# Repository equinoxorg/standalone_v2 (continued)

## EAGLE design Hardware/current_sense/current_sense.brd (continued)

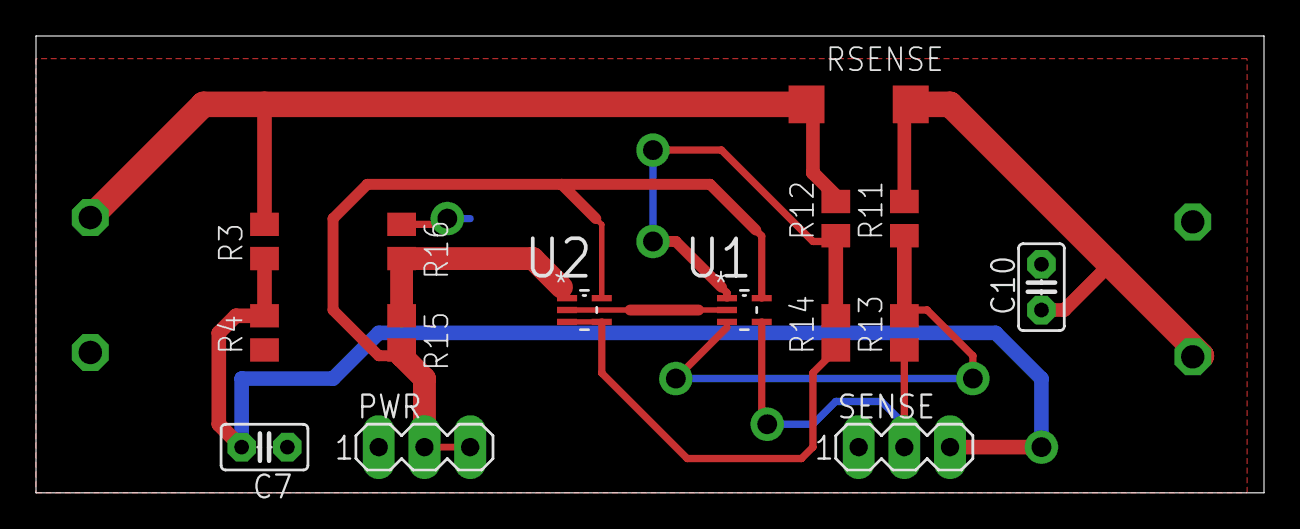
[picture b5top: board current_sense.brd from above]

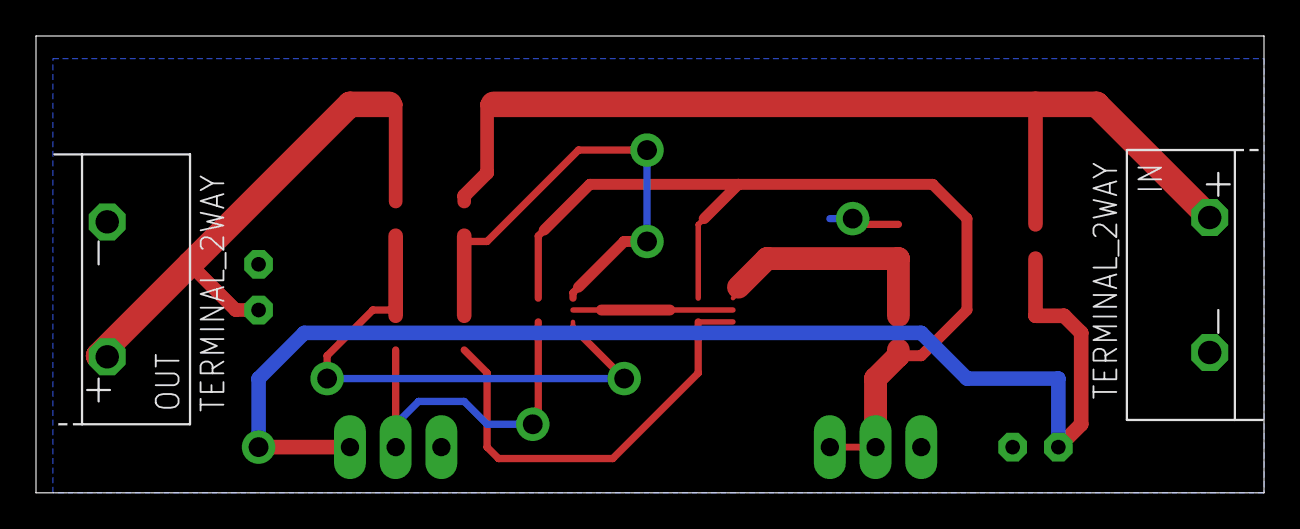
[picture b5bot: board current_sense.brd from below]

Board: 2 copper layers, 68.2 x 25.4 mm, 17 parts (2 on the bottom side), 11 nets.

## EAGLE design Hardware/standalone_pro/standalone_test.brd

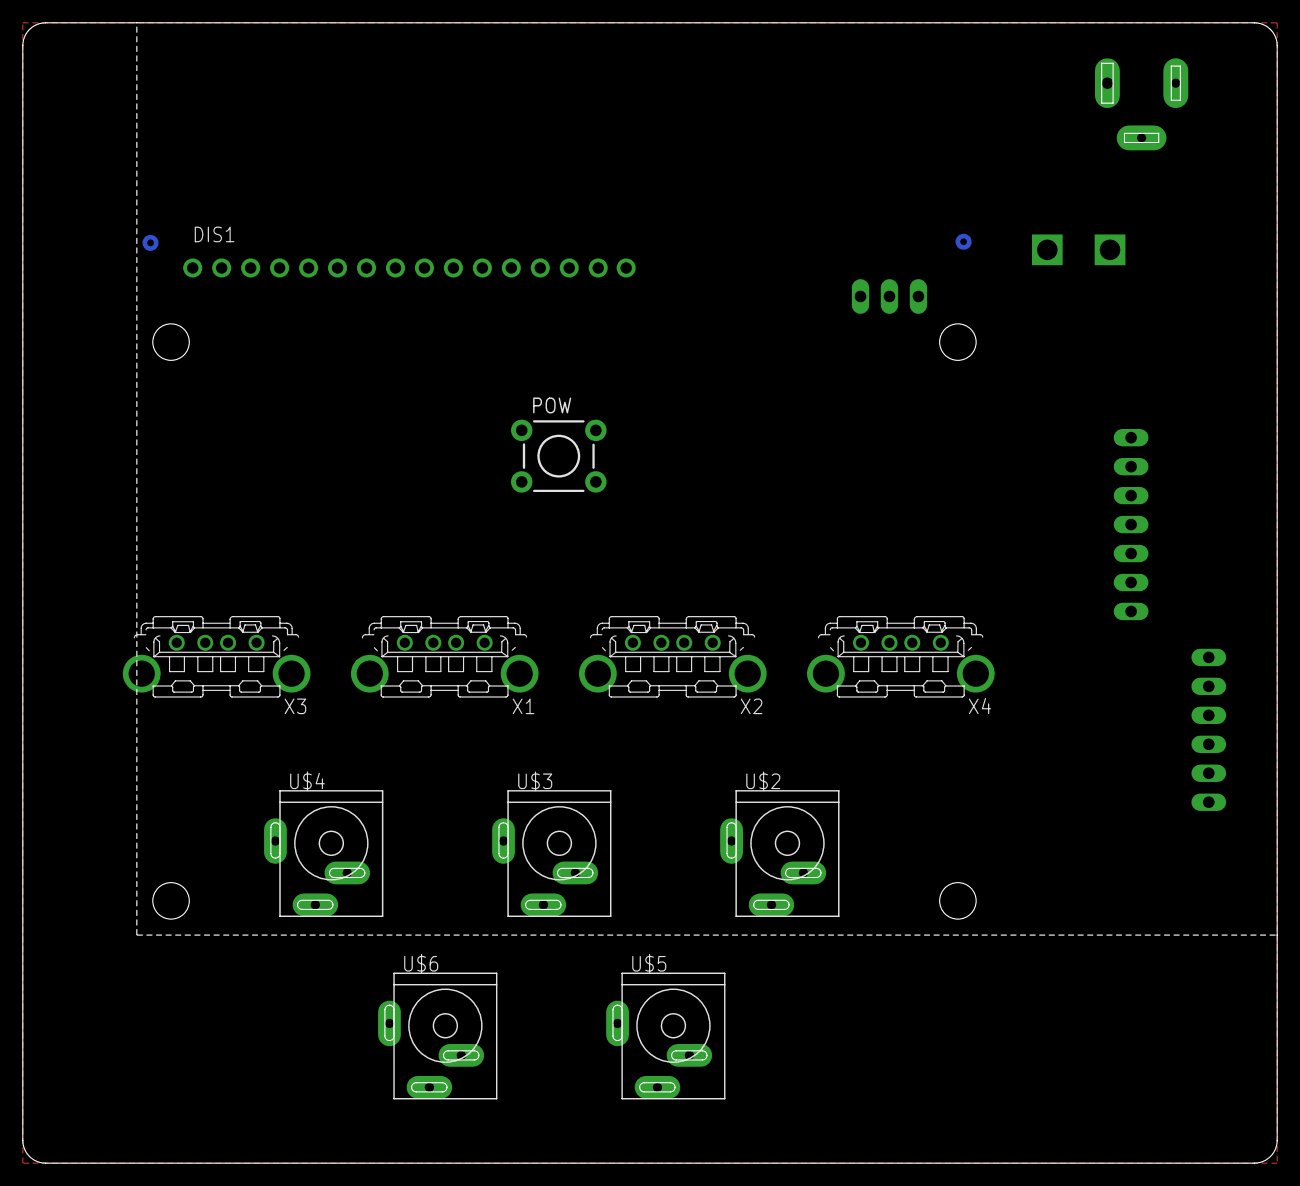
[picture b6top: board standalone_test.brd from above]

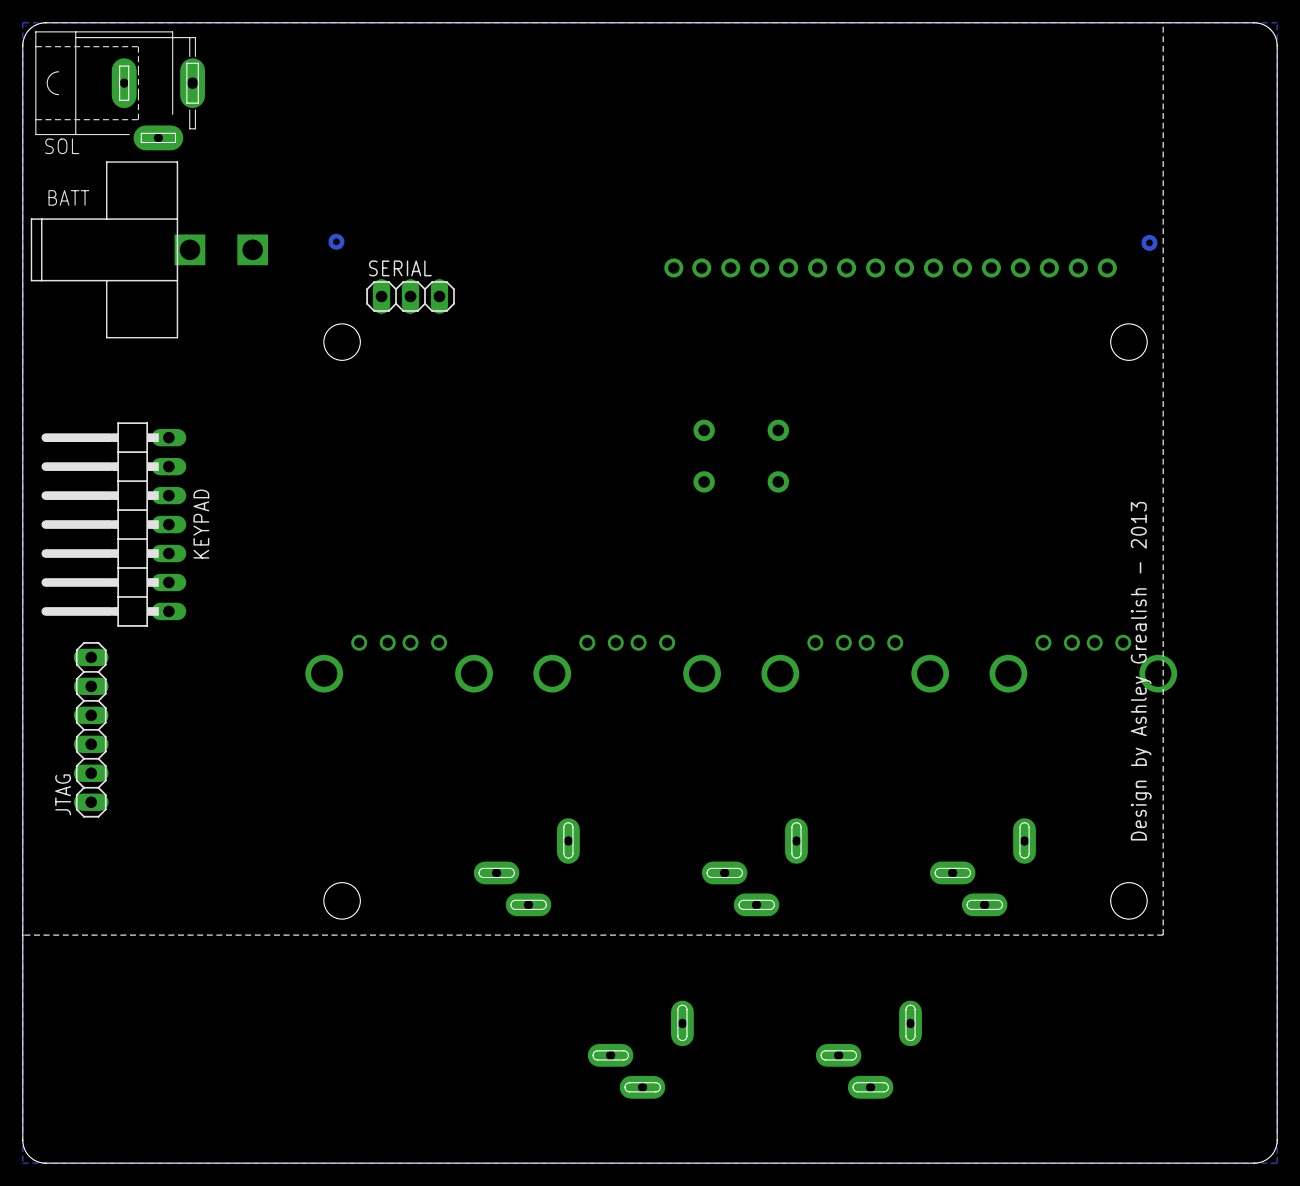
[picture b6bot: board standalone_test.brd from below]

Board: 2 copper layers, 110.0 x 100.0 mm, 17 parts (5 on the bottom side), 5 nets, no tracks yet.

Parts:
BATT: CON_MOLEX_39_29_1028; MOLEX_39_29_1028
DIS1: LCD_16X2_R2
JTAG: 1X06
KEYPAD: 1X07/90
POW: TACTILE-PTH
SERIAL: 1X03
SOL: SPC4077
U$1: EQUINOX_LOGO_LARGE
U$2, U$3, U$4, U$5, U$6: KYCON_KLDVX-0202; KYCON_KLVDX_2020_B
X1, X2, X3, X4: KUSBVX

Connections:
GND: BATT.P$2, SERIAL.3, SOL.1, SOL.2, U$4.2, U$5.2, U$5.3, U$6.2, U$6.3, X1.4, X1.M1, X1.M2, X2.4, X2.M1, X2.M2, X3.4, X3.M1, X3.M2, X4.4, X4.M1, X4.M2
unnamed: DIS1.7, DIS1.8, DIS1.9, DIS1.10
unnamed: U$3.2, U$3.3
S$6: POW.3, POW.4
S$7: U$2.2, U$2.3

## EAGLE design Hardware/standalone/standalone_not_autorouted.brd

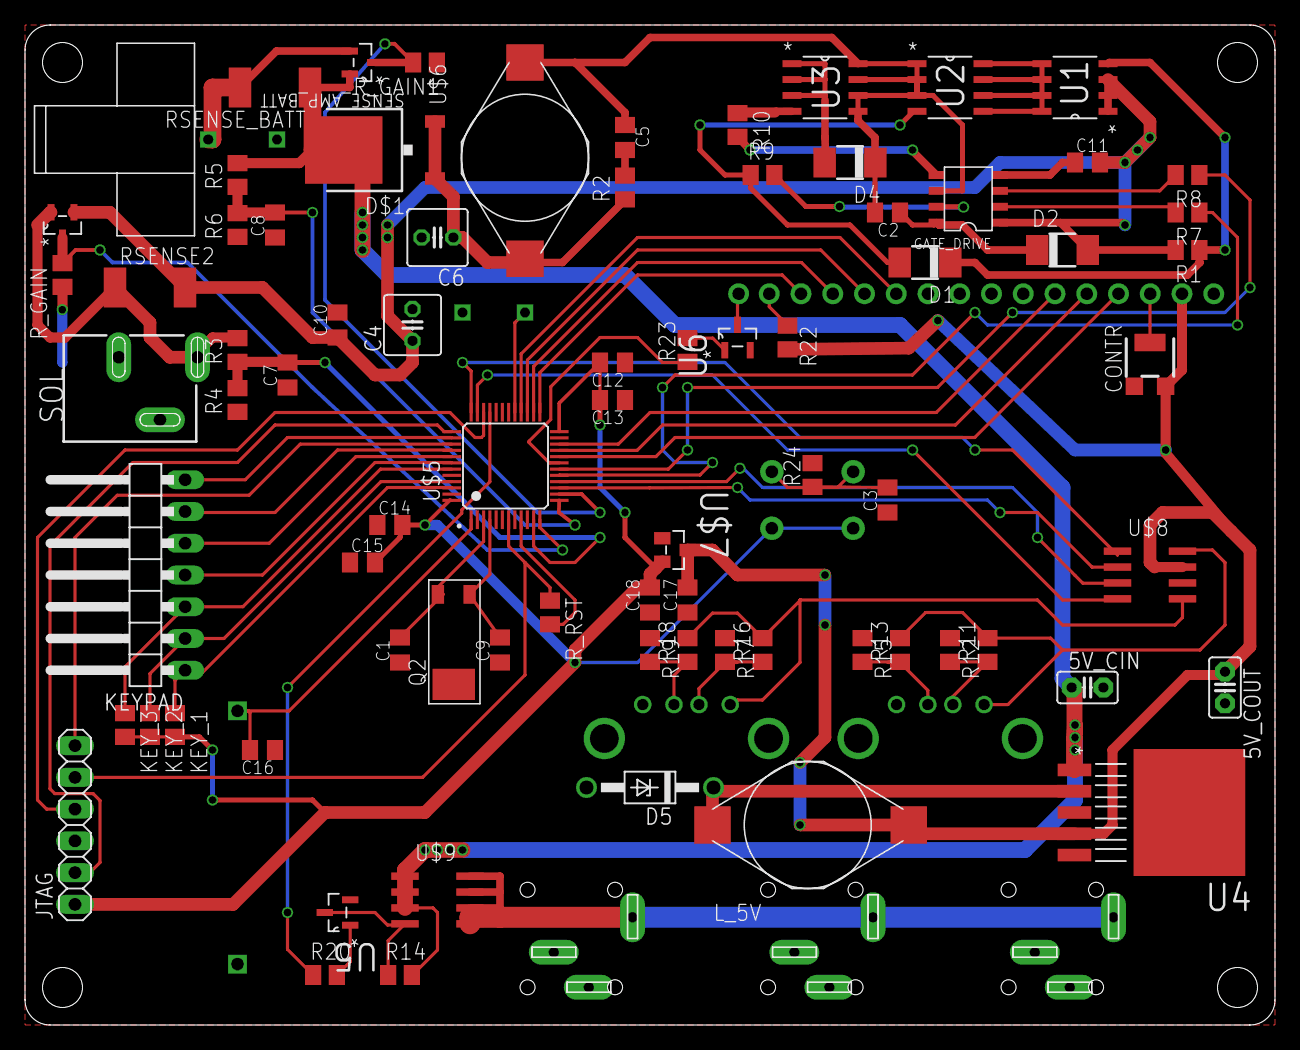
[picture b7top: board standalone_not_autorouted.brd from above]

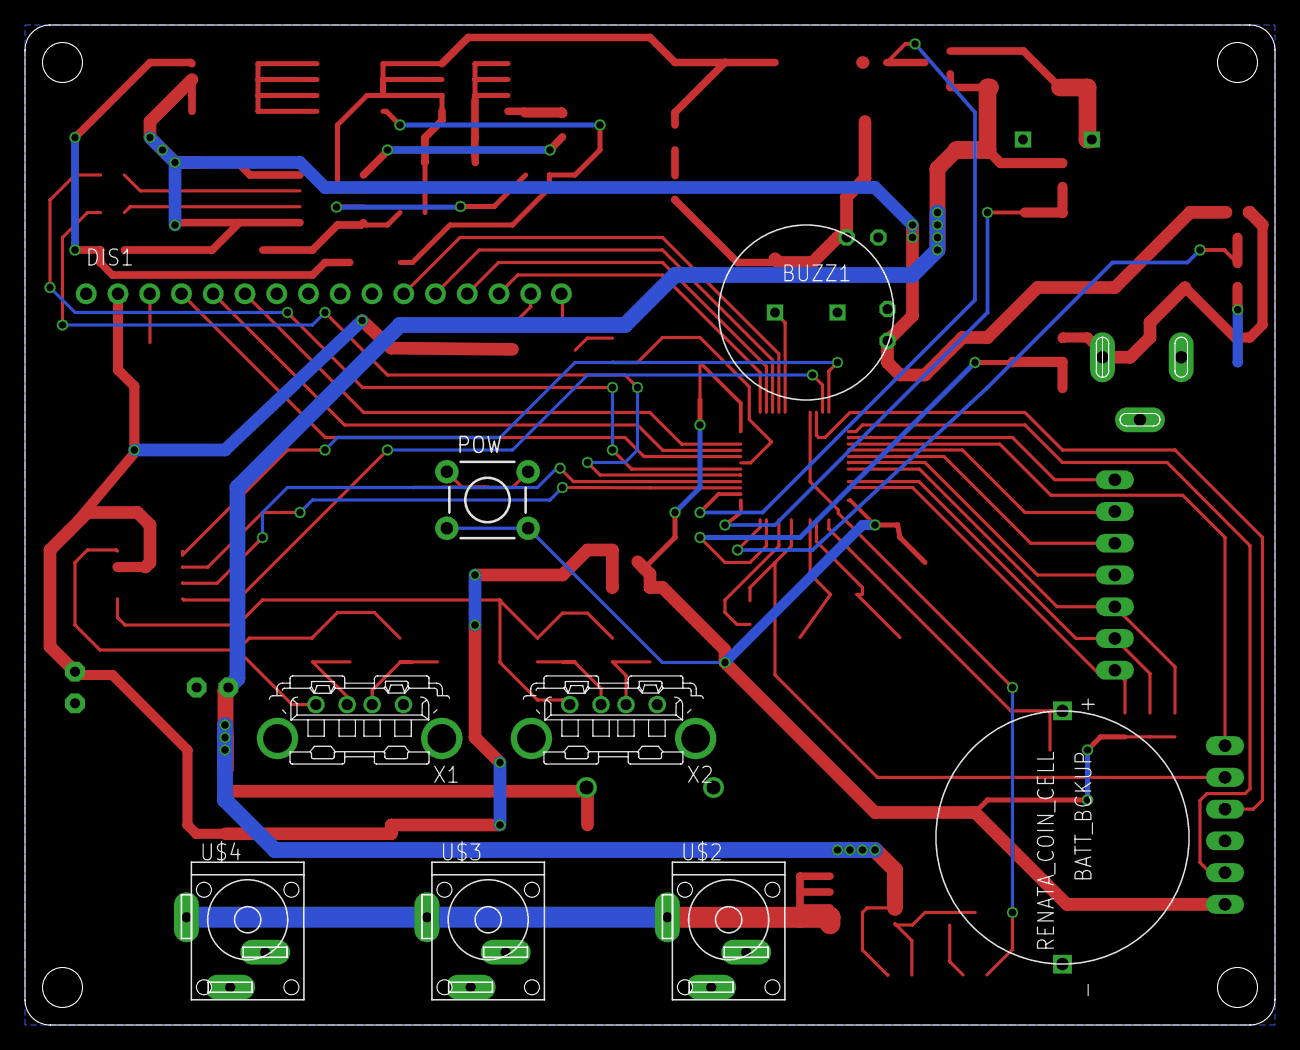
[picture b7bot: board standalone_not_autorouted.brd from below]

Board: 2 copper layers, 100.0 x 80.0 mm, 87 parts (9 on the bottom side), 68 nets.

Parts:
5V_CIN: 100u; C2.5-2
5V_COUT: 330u; C2.5-2
BATT: CON_MOLEX_39_29_1028; MOLEX_39_29_1028
BATT_BCKUP: RENATA_COIN_CELL; PANASONIC_CR2032_1298246
BUZZ1: BUZZ_14MM; 14MM_5M_PINS
C1, C9: 12.5pF; C0805K
C2, C10, C11, C12, C16, C17, C18: 1uF; C0805K
C3, C13, C14, C15: 100nF; C0805K
C4: 100uF; C025-050X050
C5, C7, C8: 0.1uF; C0805K
C6: 220uF; C025-050X050
CONTR: 10K; RTRIM3304W
D1, D2: S1A-E3/5AT; DO-214AC
D4: US1D - 1625280; DO-214AC
D5: DO41Z10
D$1: TO252
DIS1: LCD_16X2_R2
GATE_DRIVE: IR2104S
JTAG: 1X06
KEYPAD: 1X07/90
KEY_1, KEY_2, KEY_3: 10K; M0805
L_5V: 330uF; BOURNS_SDR1806
POW: TACTILE-PTH
Q2: 32.768khz; CRYSTAL_CMJ206T
R1: 470K; M0805
R2, R7, R8: 200; M0805
R3, R5: 10K; M0805
R4, R6: 1.32k; M0805
R9, R10: 5; M0805
R11, R13, R16, R18: 75k; M0805
R12, R15, R17, R19: 49.9k; M0805
R14: 100K; M0805
R20, R23, R24: 1k; M0805
R22: 0R; M0805
RSENSE2: 0.005; R2512
RSENSE_BATT: 0.005; R2512
R_GAIN, R_GAIN1: 10K; M0805
R_RST: 100K; M0805
SENSE_AMP_BATT: ZXCT1107SA-7; SOT91P240X110-3N
SENSE_AMP_SOL: ZXCT1107SA-7; SOT91P240X110-3N
SOL: POWER_JACK_2.1MMSLT; POWER_JACK_SLOT
U1, U2, U3: DMS3016SSS-13; SOIC127P600X175-8N
U4: LM2575S-15; TO170P1435X465-6N
U5, U6: NMOS_2N7002; SOT103P240X110-3N
U$1: EQUINOX_LOGO_LARGE
U$2, U$3, U$4: KYCON_KLDVX-0202; KYCON_KLVDX_2020_B
U$5: STM32F050C6T6A; LQFP48
U$6: 330uF; BOURNS_SDR1806
U$7: MCP1700T-3302E/TT; SOT95P237X112-3N
U$8: AP1212; SO8
U$9: PMOS_RSS090P03; SO8
X1, X2: KUSBVX

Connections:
12V_OUT: U$2.1, U$3.1, U$4.1, U$9.5, U$9.6, U$9.7, U$9.8
12V_OUT_EN: R20.1, U$5.33
+3V3: C12.2, C13.2, C14.2, C15.2, C18.2, JTAG.1, KEY_1.2, KEY_2.2, KEY_3.2, POW.3, POW.4, R_RST.2, U$5.9, U$5.24, U$5.48, U$7.2
+5V: 5V_COUT.1, C17.2, CONTR.3, DIS1.2, L_5V.P$2, R22.2, U4.4, U$7.3, U$8.7
BATT_I: R_GAIN1.2, SENSE_AMP_BATT.1, U$5.14
BATT_V: C8.2, R5.1, R6.2, U$5.13
CC_PWM: R7.1, U$5.17
CC_~EN: R8.1, U$5.18
GND: 5V_CIN.2, 5V_COUT.2, BATT.P$2, BATT_BCKUP.P-, BUZZ1.P$2, C1.1, C3.1, C4.2, C6.2, C7.1, C8.1, C9.1, C10.2, C11.1, C12.1, C13.1, C14.1, C15.1, C16.1, C17.1, C18.1, CONTR.1, D4.A, D5.A, DIS1.1, DIS1.7, DIS1.8, DIS1.9, DIS1.10, GATE_DRIVE.4, JTAG.3, Q2.CASE, R4.1, R6.1, R12.1, R15.1, R17.1, R19.1, R24.2, R_GAIN.1, R_GAIN1.1, SOL.GND@1, SOL.GND@2, U3.1, U3.2, U3.3, U4.3, U4.5, U4.6, U5.2, U6.2, U$2.2, U$2.3, U$3.2, U$3.3, U$4.2, U$4.3, U$5.8, U$5.23, U$5.44, U$5.47, U$7.1, U$8.6, X1.4, X1.M1, X1.M2, X2.4, X2.M1, X2.M2
LCD_BK_EN: R23.1, U$5.19
LCD_D4: DIS1.11, U$5.28
LCD_D5: DIS1.12, U$5.27
LCD_D6: DIS1.13, U$5.26
LCD_D7: DIS1.14, U$5.25
LCD_E: DIS1.6, U$5.22
LCD_RS: DIS1.4, U$5.20
LCD_RW: DIS1.5, U$5.21
unnamed: C1.2, Q2.P$2, U$5.3
unnamed: CONTR.2, DIS1.3
unnamed: GATE_DRIVE.3, R8.2
unnamed: BATT.P$1, RSENSE_BATT.2, SENSE_AMP_BATT.2
unnamed: D1.C, R1.1, U1.4
unnamed: C2.2, C5.1, D4.C, GATE_DRIVE.6, U2.1, U2.2, U2.3, U3.5, U3.6, U3.7, U3.8, U$6.P$1
unnamed: GATE_DRIVE.7, R9.2
unnamed: GATE_DRIVE.2, R7.2
unnamed: C4.1, C10.1, C11.2, D2.A, GATE_DRIVE.1, R1.2, RSENSE2.2, SENSE_AMP_SOL.2, U1.1, U1.2, U1.3
unnamed: C2.1, D2.C, GATE_DRIVE.8
unnamed: R10.1, U3.4
unnamed: C6.1, D$1.1, D$1.2, R2.1, U$6.P$2
unnamed: GATE_DRIVE.5, R10.2
unnamed: D1.A, R9.1, U2.4
unnamed: C5.2, R2.2
unnamed: R3.2, RSENSE2.1, SENSE_AMP_SOL.3, SOL.PWR
unnamed: U1.5, U1.6, U1.7, U1.8, U2.5, U2.6, U2.7, U2.8
unnamed: C9.2, Q2.P$3, U$5.4
unnamed: DIS1.15, R22.1
unnamed: R16.1, R17.2, X2.2
unnamed: D5.C, L_5V.P$1, U4.2
unnamed: BUZZ1.P$1, U$5.29
unnamed: KEYPAD.1, KEY_1.1, U$5.46
unnamed: KEYPAD.2, KEY_2.1, U$5.45
unnamed: R14.1, U5.3, U$9.4
unnamed: KEYPAD.3, KEY_3.1, U$5.43
unnamed: KEYPAD.4, U$5.42
unnamed: KEYPAD.5, U$5.41
unnamed: KEYPAD.6, U$5.40
unnamed: KEYPAD.7, U$5.38
unnamed: DIS1.16, U6.3
unnamed: R23.2, U6.1
unnamed: R11.1, R12.2, X1.2
unnamed: R13.1, R15.2, X1.3
unnamed: R20.2, U5.1
unnamed: R18.1, R19.2, X2.3
NRST: JTAG.5, R_RST.1, U$5.7
SOL_I: R_GAIN.2, SENSE_AMP_SOL.1, U$5.12
SOL_V: C7.2, R3.1, R4.2, U$5.11
SWCLK: JTAG.2, U$5.37
SWDIO: JTAG.4, U$5.34
SWO: JTAG.6, U$5.39
USB_EN1: U$5.36, U$8.1
USB_EN2: U$5.35, U$8.4
USB_FLG1: U$5.15, U$8.2
USB_FLG2: U$5.16, U$8.3
USB_OUT1: R11.2, R13.2, U$8.8, X1.1
USB_OUT2: R16.2, R18.2, U$8.5, X2.1
V_BACKUP: BATT_BCKUP.P+, C16.2, U$5.1
V_LOAD: 5V_CIN.1, D$1.3, R5.2, R14.2, RSENSE_BATT.1, SENSE_AMP_BATT.3, U4.1, U$9.1, U$9.2, U$9.3
WKUP: C3.2, POW.1, POW.2, R24.1, U$5.10

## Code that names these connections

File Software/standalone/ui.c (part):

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	EXTI_InitTypeDef   EXTI_InitStructure;
  NVIC_InitTypeDef   NVIC_InitStructure;
	
	//Enable PA0 as WKUP Pin, this will Wake up Chip from Standby Mode on rising edge
	//Configures pin as input with Pull-down resistor
	PWR_WakeUpPinCmd(PWR_WakeUpPin_1, ENABLE);
	
	//Enable interrupt on PA0 Pin
	// Enable SYSCFG clock 
  RCC_APB2PeriphClockCmd(RCC_APB2Periph_SYSCFG, ENABLE);
  
  // Connect EXTI0 Line to PA0 pin 
  SYSCFG_EXTILineConfig(EXTI_PortSourceGPIOA, EXTI_PinSource0);

  // Configure EXTI0 line 
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  */
void keypad_init (void) 
{
	//Output Pins: PA15, PB6, PB5, PB4
		
	EXTI_InitTypeDef   EXTI_InitStructure;
  GPIO_InitTypeDef   GPIO_InitStructure;
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	
	GPIO_ResetBits(GPIOB, ( GPIO_Pin_4 | GPIO_Pin_5 | GPIO_Pin_6 ));
	
	//Input Pins with pull-ups and interrupt: PB7, PB8, PB9
	
	// GPIOB Clocks enable 
  RCC_AHBPeriphClockCmd( RCC_AHBPeriph_GPIOB, ENABLE);
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
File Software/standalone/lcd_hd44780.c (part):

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
//Data Pin Definitions
	//PORT B
#define LCD_D4	GPIO_Pin_15
#define LCD_D5	GPIO_Pin_14
#define LCD_D6	GPIO_Pin_13
#define LCD_D7	GPIO_Pin_12

//Control Pin Definitions
	//PORT 
#define LCD_RS	GPIO_Pin_2
// \/ THIS PIN IS NEVER USED!!! \/
#define LCD_RW	GPIO_Pin_10
#define LCD_E		GPIO_Pin_11

#define LCD_BK_EN GPIO_Pin_1
#define LCD_PWR		GPIO_Pin_11

//Macro Definitions
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{
	GPIO_InitTypeDef GPIO_InitStructure;
	
	GPIO_InitStructure.GPIO_Pin = LCD_D4 | LCD_D5 | LCD_D6 | LCD_D7;
	if (io == INPUT)
		GPIO_InitStructure.GPIO_Mode = GPIO_Mode_IN;
	else
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uint8_t read_data_inputs (void) {
	uint8_t temp = 0;
	
	temp = GPIO_ReadOutputDataBit(GPIOB, LCD_D4);
	
	temp |= GPIO_ReadOutputDataBit(GPIOB, LCD_D5) < 1;
	temp |= GPIO_ReadOutputDataBit(GPIOB, LCD_D6) < 2;
	temp |= GPIO_ReadOutputDataBit(GPIOB, LCD_D7) < 3;
	
	return temp;
}
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
	//change LCD mode
	//SET_RW();		//Read mode
	GPIO_SetBits(GPIOB, LCD_RW);
		
	//CLEAR_RS();		//Read status
	GPIO_ResetBits(GPIOB, LCD_RS);

	//Let the RW/RS lines stabilize
	delay_us(0.5);		//tAS
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	{

		//SET_E();
		GPIO_SetBits(GPIOB, LCD_E);
		

		//Wait tDA for data to become available
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
		//Pull E low
		//CLEAR_E();
		GPIO_ResetBits(GPIOB, LCD_E);
		
		delay_us(1);	//tEL

		//SET_E();
		GPIO_SetBits(GPIOB, LCD_E);
		
		delay_us(0.5);

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		delay_us(0.5);
		
		//CLEAR_E();
		GPIO_ResetBits(GPIOB, LCD_E);
		
		delay_us(1);	//tEL
		
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
	//write mode
	//CLEAR_RW();
	GPIO_ResetBits(GPIOB, LCD_RW);
	
	//Change Port to output
	//LCD_DATA_TRIS&=0xF0;
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{
	if (en)
	{
		GPIO_SetBits(GPIOB, LCD_BK_EN );
		
		//Stop old timer
		if (bk_tmr != NULL)
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		//Stop old timer
		os_tmr_kill(bk_tmr);
		
		GPIO_ResetBits(GPIOB, LCD_BK_EN );
	}
}


void lcd_bk_tmr_expire(void)
{
	GPIO_ResetBits(GPIOB, LCD_BK_EN );
}

void lcd_power(char en)
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void cycle_e (void)
{
	tsk_lock();
  GPIO_SetBits(GPIOB, LCD_E);
  delay_us(1);
  GPIO_ResetBits(GPIOB, LCD_E);
  delay_us(1);
	tsk_unlock();
	lcd_wait();
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	//Configure Pins
	GPIO_StructInit(&GPIO_InitStructure);
	
	GPIO_InitStructure.GPIO_Pin = LCD_D4 | LCD_D5 | LCD_D6 | LCD_D7 | LCD_RS | LCD_RW | LCD_E | LCD_BK_EN ;
	GPIO_InitStructure.GPIO_Mode = GPIO_Mode_OUT;
  GPIO_InitStructure.GPIO_OType = GPIO_OType_PP;
  GPIO_InitStructure.GPIO_Speed = GPIO_Speed_50MHz;
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// 	{
		//LCD Not Inited so Init it
		
		GPIO_ResetBits(GPIOB, (LCD_E | LCD_RS | LCD_RW ) );
		GPIO_ResetBits(GPIOB, (LCD_D4 | LCD_D5 | LCD_D6 | LCD_D7 | LCD_BK_EN) );

		GPIO_SetBits(GPIOA, LCD_PWR);	
		
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		lcd_send_cmd(0x30);
		delay_us(100);
			
		GPIO_SetBits(GPIOB, LCD_D5);
		cycle_e();
		//lcd_wait();
		
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	//combinations of data pins can be used
	
	if ( (c >> 0) & 0x01 )
		GPIO_SetBits(GPIOB, LCD_D4 );
	else
		GPIO_ResetBits(GPIOB, LCD_D4 );
	
	if ( (c >> 1) & 0x01 )
		GPIO_SetBits(GPIOB, LCD_D5 );
	else
		GPIO_ResetBits(GPIOB, LCD_D5 );
	
	if ( (c >> 2) & 0x01 )
		GPIO_SetBits(GPIOB, LCD_D6 );
	else
		GPIO_ResetBits(GPIOB, LCD_D6 );
	
	if ( (c >> 3) & 0x01 )
		GPIO_SetBits(GPIOB, LCD_D7 );
	else
		GPIO_ResetBits(GPIOB, LCD_D7 );
}


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{
	//Send Upper Bits
	lcd_send_4_bits(c>>4);
	GPIO_ResetBits(GPIOB, LCD_RS);
	cycle_e();
	
	//Send Lower Bits
	lcd_send_4_bits(c);	
	GPIO_ResetBits(GPIOB, LCD_RS);
	cycle_e();
	//lcd_wait();
}
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{
	//Send Upper Bits
	lcd_send_4_bits(c>>4);
	GPIO_SetBits(GPIOB, LCD_RS);
	cycle_e();
	
	//Send Lower Bits
	lcd_send_4_bits(c);	
	GPIO_SetBits(GPIOB, LCD_RS);
	cycle_e();
}

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
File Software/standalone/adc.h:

#ifndef __adc_h
#define __adc_h

#include "standalone_config.h"

#ifndef ADC_VREF
	#define ADC_VREF 3.3f
#endif

#define ADC_SOL_V		ADC_Channel_1 //PA1
#define ADC_SOL_I		ADC_Channel_2 //PA2
#define ADC_BATT_V	ADC_Channel_3 //PA3
#define ADC_BATT_I	ADC_Channel_4 //PA4
#define ADC_TEMP		ADC_Channel_TempSensor


#define SCALE_V_SOL(x)	((x) * ((10.0f + 1.33f) / 1.33f ) )
#define SCALE_I_SOL(x)	( x / (0.004f * 0.1f * 1330.0f) )
#define SCALE_V_BATT(x)	((x) * ((10.0f + 1.33f) / 1.33f ) )
#define SCALE_I_BATT(x) ((x-(ADC_VREF/2)) * (0.01f * 50.0f) )

//Convert a current to an equivilent ADC reading
#define I_BATT_TO_ADC(x)	( (uint16_t) ( ( ((x/(0.01f * 50.f))+(ADC_VREF/2)) / ADC_VREF ) * 0xFFF) )

#define NO_SAMPLES 16
#define NO_CHANNELS 5

//Public Variables
extern volatile uint16_t RegularConvData_Tab[NO_SAMPLES * NO_CHANNELS];
extern OS_TID adc_test_t;


/* Private variables ---------------------------------------------------------*/

/* Public function prototypes -----------------------------------------------*/
void init_adc( void );
float get_adc_voltage (uint32_t);
__task void adc_test (void);

#endif

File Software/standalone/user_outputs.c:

#include "user_outputs.h"


/**
  * @brief  Configure PA5 and PA6 falling edge in interrupt mode
	*					and PF6 and PF7 as output pins
  * @param  None
  * @retval None
  */
void usb_outputs_init (void)
{
	EXTI_InitTypeDef   EXTI_InitStructure;
  GPIO_InitTypeDef   GPIO_InitStructure;
  NVIC_InitTypeDef   NVIC_InitStructure;
	
	//Set up USB Enable Pins
	
	/* GPIOF Clocks enable */
  RCC_AHBPeriphClockCmd( RCC_AHBPeriph_GPIOF, ENABLE);
  
  /* GPIOF Configuration*/
  GPIO_InitStructure.GPIO_Pin = GPIO_Pin_6 | GPIO_Pin_7;
  GPIO_InitStructure.GPIO_Mode = GPIO_Mode_OUT;
  GPIO_InitStructure.GPIO_Speed = GPIO_Speed_50MHz;
  GPIO_InitStructure.GPIO_OType = GPIO_OType_PP;
  GPIO_InitStructure.GPIO_PuPd = GPIO_PuPd_NOPULL ;
  GPIO_Init(GPIOF, &GPIO_InitStructure);
	
	//Set up USB Error Interrupts
  // GPIOA Clocks enable 
  RCC_AHBPeriphClockCmd( RCC_AHBPeriph_GPIOA, ENABLE);
  
  // GPIOA Configuration
  GPIO_InitStructure.GPIO_Pin = GPIO_Pin_5 | GPIO_Pin_6;
  GPIO_InitStructure.GPIO_Mode = GPIO_Mode_IN;
  GPIO_InitStructure.GPIO_Speed = GPIO_Speed_50MHz;
  GPIO_InitStructure.GPIO_OType = GPIO_OType_PP;
	//Enable Pull-ups on USB Flag Pins
  GPIO_InitStructure.GPIO_PuPd = GPIO_PuPd_UP ;
  GPIO_Init(GPIOA, &GPIO_InitStructure);

  /* Enable SYSCFG clock */
  RCC_APB2PeriphClockCmd(RCC_APB2Periph_SYSCFG, ENABLE);
  
  /* Connect EXTI5 Line to PA5 pin */
  SYSCFG_EXTILineConfig(EXTI_PortSourceGPIOA, EXTI_PinSource5);
	/* Connect EXTI6 Line to PA6 pin */
  SYSCFG_EXTILineConfig(EXTI_PortSourceGPIOA, EXTI_PinSource6);
	
  /* Configure EXTI5 & EXTI6 line */
  EXTI_InitStructure.EXTI_Line = EXTI_Line5 | EXTI_Line6;
  EXTI_InitStructure.EXTI_Mode = EXTI_Mode_Interrupt;
  EXTI_InitStructure.EXTI_Trigger = EXTI_Trigger_Falling;
  EXTI_InitStructure.EXTI_LineCmd = ENABLE;
  EXTI_Init(&EXTI_InitStructure);

  /* Enable and set EXTI4_15 Interrupt */
  NVIC_InitStructure.NVIC_IRQChannel = EXTI4_15_IRQn;
  NVIC_InitStructure.NVIC_IRQChannelPriority = 0x00;
  NVIC_InitStructure.NVIC_IRQChannelCmd = ENABLE;
  NVIC_Init(&NVIC_InitStructure);
}

void dc_outputs_init (void)
{
	GPIO_InitTypeDef GPIO_InitStructure;
	
	/* GPIOF Clocks enable */
  RCC_AHBPeriphClockCmd( RCC_AHBPeriph_GPIOA, ENABLE);
  
  /* GPIOF Configuration*/
  GPIO_InitStructure.GPIO_Pin = GPIO_Pin_12;
  GPIO_InitStructure.GPIO_Mode = GPIO_Mode_OUT;
  GPIO_InitStructure.GPIO_Speed = GPIO_Speed_50MHz;
  GPIO_InitStructure.GPIO_OType = GPIO_OType_PP;
  GPIO_InitStructure.GPIO_PuPd = GPIO_PuPd_NOPULL ;
  GPIO_Init(GPIOA, &GPIO_InitStructure);
  
}

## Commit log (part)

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2013-03-11 Added Peturb and Observe Code
2013-03-11 Added lates MPPT Tracking PCB design
    Also cleaned hardware folder, removing non-working current sense
    designs.
2013-03-26 Updated the .gitignore file
2013-03-26 Some updates to MPPT hardware and software
    The design now can charge lead acid batteries but no high/low voltage
    cut-out is enabled.
2013-03-28 Fist Full Standalone V2 Proo
2013-03-28 Added item to hardware todo list
2013-03-28 Add RTC and LCD Drivers
    These are both untested as no access to hardware currently
2013-03-29 ADC now read Continuously with DMA Access
    Should reduce CPU load fix the ADC not reading error.
    May need to add low pass filtering with 20kHz cut off to remove
    switching noise. Simply averaging many reads of ADC will no longer work.
2013-03-31 Fixed RTC Enable Code
    Correct Peripheral Clock was not being enabled
2013-03-31 Cleaned up ADC Code. Added Interrupted Charging
2013-04-01 Added two extra ADC Channels to read from
    get_adc_voltage can now read current and voltage from battery or solar
    panel.
2013-04-01 Interrupted Charging Algorithm Ready for Testing
    Not yet tested due to lack of Sunlight, thanks UK.
2013-04-20 Some Hardware Fixes
    Fixed the Battery Connector.
    Added more items to ToDo list
2013-04-20 Added Latest Bill of Materials
2013-04-21 Cleaned Library and Complete some ToDo list
    Added power LED and changed MPPT reverse current diode
2013-04-23 Many PCB Improvements
    Tidied up Silkscreen.
    Changed some through hole components to surface mount.
    Changed the 15V regulator for 5V as originally intended.
    Checked power rating of converters. Need to update 5V out to 3A.
    On PCB, tidied up the 12V track and thickened so that it can carry
    larger current.
2013-05-14 Increase 5V Output to 3A max
    Switched SMPS Controller, Inductor and Capacitor.
2013-05-14 Added Readme File
2013-05-14 Added License files
2013-05-17 Moved Mounting Holes and Removed DC Jack Holes
2013-05-20 Moved PWM Output to Correct Pin
    Code now matches hardware
2013-05-24 LCD Basic Functionality Added.
    Needs some work and improvements to the library including added GoTo
    statements and Adding a busy loop check.
2013-05-24 Increased Default stack size
    Now has 128 word stack.
    Also made small error handling changes.
2013-05-24 lcd_hd44870 fixed and made more usable
    lcd_hd44780 library updates and tested.
    Extra functions such as write string/int and gotos added
2013-05-25 ADC Channels Corrected for STM32F050C6
2013-05-25 Enabled Pull-Up Resistors on USB Error Flag Pins
2013-05-27 Tested LCD High Level Functions
2013-05-27 USB Error Protection Implemented with Interrupts
    Interrupt on USB_FLG falling edge. Causes USB port that caused the error
    to be disabled.
2013-05-27 Fixed Pin Definitions for Serial Port
    Serial Port Now Working
2013-05-27 Minor Code Clean Ups
2013-05-27 Updated .gitignore to not commit .map files
2013-05-28 Improved LCD Init. Fixes unreliability problems
2013-05-28 Major PCB Re-arrangements and Fixes
2013-05-29 PCB 100% Routed
2013-05-29 PCB Fixes
    LCD Power Switch Added.
2013-05-29 PCB Rev2 Complete. Ready for manufacture
2013-05-29 Cleanup of un-needed files
2013-05-30 First izuba.box pro commit
    Mostly just a test for the connectors layout
2013-05-30 Small Calibrations added to ADC Code
2013-05-30 First Test of Keypad Code
    Working but needs to be implemented with interrupts and de-bouncing
    Hardware pull up resistors no longer required. Internal uC pull ups are
    used.
2013-05-30 Minor changes to charging voltage levels
2013-05-31 Added function to quick scan for MPP
    This function is used to set the initial conditions for the P&O
    function.
2013-05-31 More usable trace output for charge control algorithm
2013-05-31 Combined LCD task with UI task
2013-06-02 Added Power Switch Functionality.
2013-06-02 Fixed pwm_out test task
2013-06-02 Added temperature sensor reading to ADC functions
2013-06-02 Added Constant Current Control to P&O Algorithm
    Allows the passing of a maximum battery current which will be allowed
    during MPPT.
2013-06-02 Added better keypad de-bouncing
    Still needs some work to make more responsive.
2013-06-02 Final Keypad de-bouncing
    Keypad de-bouncing works. Low overheads and feels responsive.
2013-06-03 Added NIGHT_MODE transition to CC task
2013-06-03 Fixed NIGHT_MODE transition
2013-06-05 Analog Watchdog Code Added
    Not Yet Tested
2013-06-05 Added LVDC and Fixed the exiting of Night Mode
2013-06-05 Removed Keypad Pullups and Fixed MPPT out tracks
2013-06-05 Fixed Pulsed Charging Code
2013-06-05 Cleaned up user_outputs code
2013-06-06 Added LCD Battery Icon Code
    Taken from Raymond's V1 code
2013-06-06 Fixed ADC Task and some ADC Calibration Factors
2013-06-06 Fixed Stack sizes for Tasks
    Can now run 4 tasks at the same time.
    Stack size is normally set by the creation of the task.
    Default stack size is now much smaller.
2013-06-06 Changing Stack type to U64 as recommended
2013-06-06 Use DMA to fill ADC Averaging Arrays
    Reduces the overhead of using interrupts to copy the data between memory
    space.
2013-06-06 Improved the Trace data for the charge controller
2013-06-07 Added Buzzer Functionality
2013-06-07 Added Payment Control Task and Fixed CC Logging
2013-06-08 Updated MPPT Inductor and added comments
2013-06-08 BOM Updated
2013-06-08 Added EEPROM Emulation Code and Box ID Test
2013-06-08 Cleanup of many code files
2013-06-13 Added Dimensions images to hardware folders
2013-06-13 BOM Updates
2013-06-13 Standalone pro physical layout finalised
2013-06-13 Moved drill holes to correct position
2013-06-14 Latest V2.4 PCB design (Sent to EuroCircuits)
2013-06-15 Updated ADC Scaling factors
2013-06-15 LCD Power Function added
2013-06-15 LCD Power function used in UI task
2013-06-15 Added Temperature and Current Charging compensation
2013-06-21 Added battery icon code, backlight timeout
2013-06-21 Error reporting for RTC crystal stability
    Will report an error on the serial port and prevent code lock-up
2013-06-22 Pro Standalone board updated
2013-06-22 Added Relay to Standalone Pro
2013-06-25 Added Unlock Codes
    These files are not on Github to protect the code generation algorithm.
2013-07-05 Connections added (with corrected faults)
2013-07-05 More corrections on relay
2013-07-05 Fixed Phantom Key typing bug. Clean up of buzzer
    Was caused by not having the KEY_NONE error check
2013-07-05 Decreased Serial Receive Buffer Size
    Large buffer not needed as code never receives data with current code.
2013-07-05 RTC temp switched to Internal RC Oscillator
    When hardware fixed switch back to External Oscillator but with a
    internal Oscillator backup for failure of external XTAL.
2013-07-05 Parallel Resistor added to buzzer circuit.
2013-07-06 Drc; overlap errors corrected
2013-07-06 Gnd connected
2013-07-06 New overlap fixed
2013-07-10 Changed RTC XTAL Hardware
    Both Home and Pro boards have working XTAL. OC_FARNELL attributes give
    correct part numbers.
2013-07-10 Added RTC LSE clock failure handling
    If LSE cannot be started then fall back to the LSI. Not ideal but better
    than total failure,
2013-07-17 izuba.box home production data added
    This production data will be used to obtain a quote for assembly from
    quick-tech.
2013-07-21 Fixed LCD Integer Write function
2013-07-21 Added full unlock code verification code
    The firmware now uses the full unlock code checking algorithm.
2013-07-21 Add a zip file of home box production files
2013-07-21 Fixed update of remaining days on LCD
2013-07-22 Pro Unit Hardware design completed
2013-07-22 Added Media Images
2013-07-22 Readme Update
2013-07-22 Updated Home Bill of Materials
    Part numbers for all items now up-to-date and Quick-Tech catalogue parts
    have been used.
2013-07-25 Simplified code with global config header file
2013-07-25 Compiler warnings for unreachable code resolved
2013-07-27 Code to enter BoxID if one is not set
    Only should be used for first ever startup
2013-07-27 Remove duplicate includes of trace lib
2013-07-28 BOM updated with Prices
2013-08-03 Pro hardware ready for first prototype
2013-08-03 Trace level now set in main config file
2013-08-03 Current compensation on CC re-implemented
    This is used to adjust the upper voltage threshold for charging and also
    used to calculate SOC for display on the LCD.
2013-08-25 Add Pro BOM
2013-08-27 Updates Pro MPPT Inductor Part #
2013-09-12 Battery indicator and other features
    Added features on battery display, box-id must be ticked, no output in
    setup, and valid invalid code display and no reappearing crossed code
    input
2013-09-18 Stable Version
    - Added the LVDC feature
    - Added the LVDC flag into the EEPROM to ensure that the box remembers
    the state
    - Commented out the TRACE_ERROR function calls in main to increase
    memory available to allow the INFO trace level to compile
2013-09-19 Increased Memory
    Instead of removing the TRACE_ERROR function call in interrupted
    charging, it was better to remove the lcd_write_strings in the debug
    mode i.e. "Box ID" and "unlock Count" and leave the actual values
    instead. This frees up some memory to allow the compilation of the code
    with the TRACE_INFO level
2013-09-19 Fixed an Issue with the last unlock code
    The Unlock code would re-appear after the unlock time expires and
    sometimes would put the box in an unknown state. This has been fixed in
    this commit by simply re-initializing the entry_code, display_str and
    digit_count variables to 0 after a valid code has been entered.
2013-09-22 Possible LCD Fix
    Started Implementing better LCD Driver which reads data from LCD but
    Init function does not make use of this yet
    Changed the Init Function slightly, this seems to fix the corruption of
    Reset Issue. This issue appears to happed when calling lcd_init() twice
    without removing power to the PCB.
2013-09-23 Linker problems fixed by changing Compiler Option
    Compile One ELF per function enabled to allow the linker to remove all
    unused functions. This fixes the Linker error messages of now enough
    space. "No space in execution regions with .ANY selector matching
    Section <name>(<objname>)"
2013-09-23 LCD Driver Tweaks
    Hopefully gives more reliable performance.
2013-09-23 More LCD Tweaks
    Fixes some issues introduced in last commit
2013-09-23 LCD Driver Using Polls LCD for timing
    LCD Driver uses polling of the LCD rather than hard coded timings. This
    was meant to fix the corruption issues but does not appear too.
2014-08-24 Ignore auto-generated files
    Full details on file types used by Keil here:
    http://www.keil.com/support/man/docs/uv4/uv4_b_filetypes.htm
2014-08-24 Readme copy-edit
2014-08-24 Modified LCD initialisation to avoid random characters
    Additional 'Function Set' commands added to the LCD initialisation
    routine. This avoids the LCD defaulting to 8-bit mode rather than 4-bit
    mode if the microcontroller is reset without also power cycling the LCD.
    Entering 8-bit mode results in incorrect characters being displayed due
    to a different interpretation of data from the data pins, and half of
    the data pins required for 8-bit mode not being connected.
2014-09-06 Fixed LVDC infinite loop
    Resolved problem where the LVDC event flag (UI_LVDC) was used instead of
    the LVDC user interface state (STATE_LVDC). This previously resulted in
    an infinite loop when the system entered this state. Also set the LCD to
    be cleared before being turned on, to avoid the previous data being
    displayed.
2014-09-20 Set LVDC to approximately 50% DoD
    Low voltage disconnect threshold reduced from 80% to approximately 50%
    depth of discharge. This works out as around 11.4-11.8V, depending on
    battery current, compared to a range of 10.8-11.2V for the previous
    threshold value. The aim of this modification is to improve battery
    longevity.
